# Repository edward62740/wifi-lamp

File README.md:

# WMNS Lamp

This is an mood lamp that takes ambient light readings from a database and adjusts its brightness and state accordingly. Extention of [WMNS](https://github.com/edward62740/Wireless-Mesh-Network-System).

## Description
Self-explanatory project which feeds off existing real-time data to decide it's brightness level.
Hardware based off ESP8266 with USB bridge and orange LED with driver. Enclosure printed (SLA) from black and clear resin.

</br>
Code should be modified based off desired operation. In this case, the lamp is set to activate at between 2 and 30 lux, which translates to dawn and dusk.

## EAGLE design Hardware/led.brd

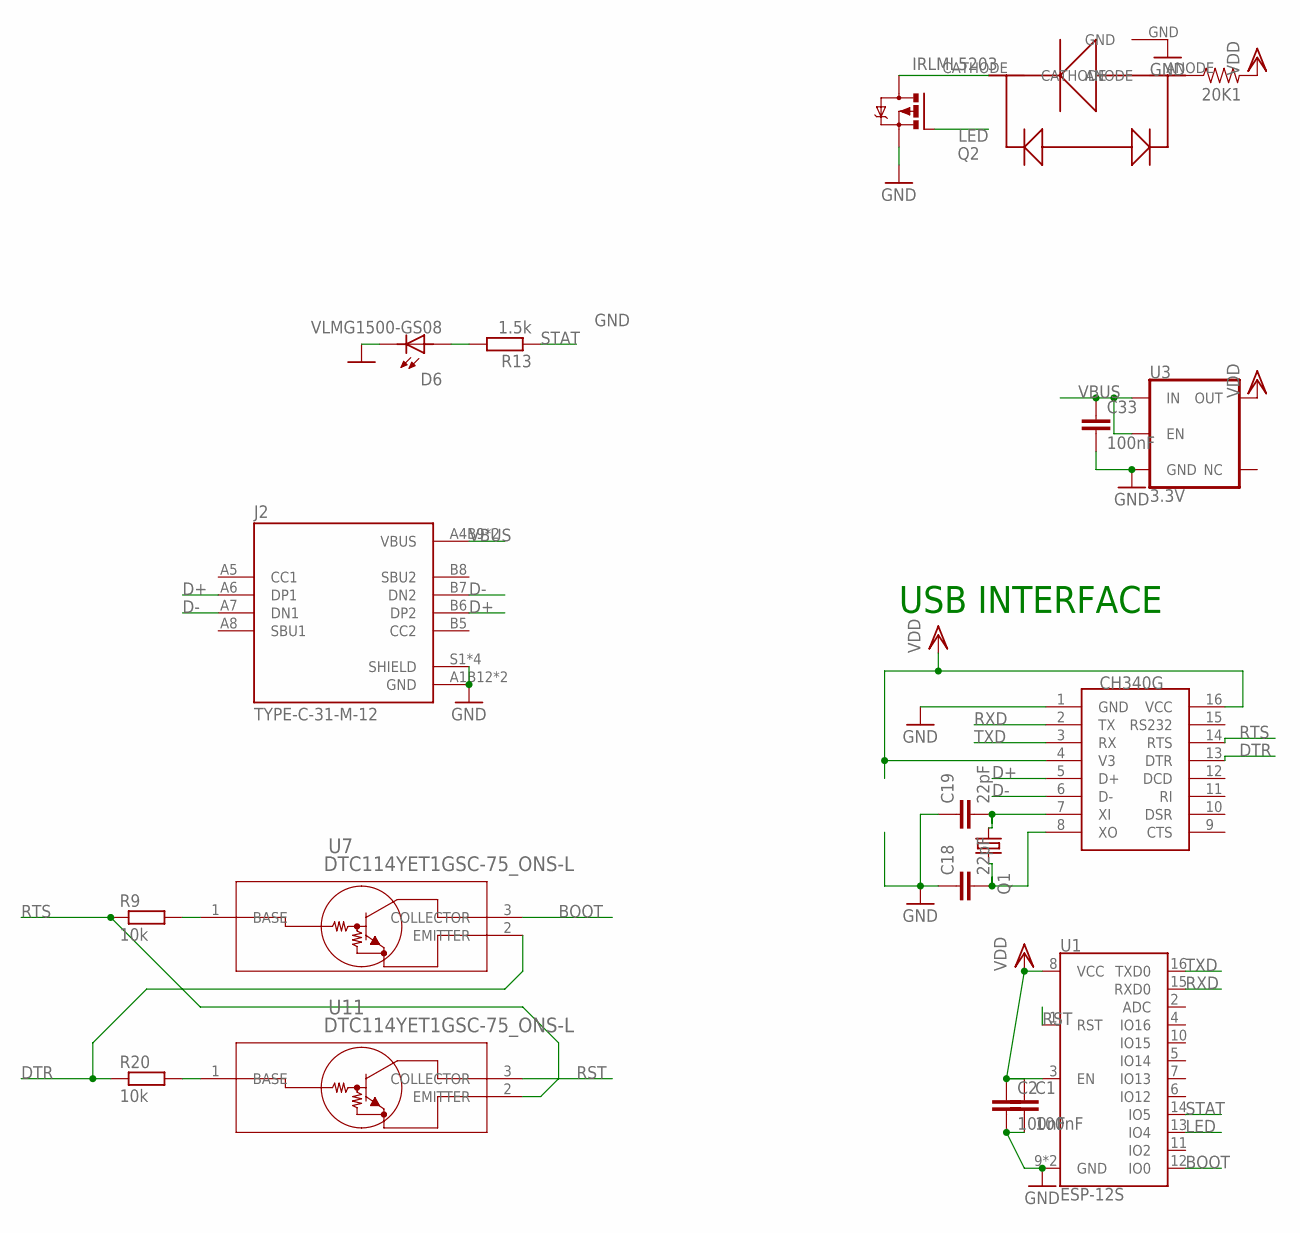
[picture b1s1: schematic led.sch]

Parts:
20K1: 0.05; 1210
C1, C2, C33: 100nF; C0402
C18, C19: 22pF; C0402
D6: VLMG1500-GS08; LEDC1005X35N
J2: TYPE-C-31-M-12; HRO_TYPE-C-31-M-12
Q1: KX-7; 3.2X2.5_KX-7
Q2: IRLML5203; MICRO3
R9, R20: 10k; R0402
R13: 1.5k; R0402
U1: ESP-12S
U3: 3.3V; SOT23-5
U5: H; SOIC16
U7, U11: DTC114YET1GSC-75_ONS-L; SC-75_ONS-L
U$1: ELSW(1W)

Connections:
BOOT: U1.12 (IO0), U7.3 (COLLECTOR)
D+: J2.A6 (DP1), J2.B6 (DP2), U5.5 (D+)
D-: J2.A7 (DN1), J2.B7 (DN2), U5.6 (D-)
DTR: R20.1, U5.13 (DTR), U7.2 (EMITTER)
GND: C1.2, C2.2, C18.1, C19.1, C33.2, D6.2, J2.A1B12 (GND), J2.B1A12 (GND), J2.S1 (SHIELD), J2.S2 (SHIELD), J2.S3 (SHIELD), J2.S4 (SHIELD), Q2.2 (S), U1.9 (GND), U1.P$1 (GND), U3.2 (GND), U5.1 (GND), U$1.GND
LED: Q2.1 (G), U1.13 (IO4)
unnamed: 20K1.1, U$1.ANODE
unnamed: Q2.3 (D), U$1.CATHODE
unnamed: C18.2, Q1.3 (2), U5.8 (XO)
unnamed: C19.2, Q1.1, U5.7 (XI)
unnamed: D6.1, R13.2
unnamed: R20.2, U11.1 (BASE)
unnamed: R9.2, U7.1 (BASE)
RST: U1.1 (RST), U11.3 (COLLECTOR)
RTS: R9.1, U5.14 (RTS), U11.2 (EMITTER)
RXD: U1.15 (RXD0), U5.2 (TX)
STAT: R13.1, U1.14 (IO5)
TXD: U1.16 (TXD0), U5.3 (RX)
VBUS: C33.1, J2.A4B9 (VBUS), J2.B4A9 (VBUS), U3.1 (IN), U3.3 (EN)
VDD: 20K1.2, C1.1, C2.1, U1.3 (EN), U1.8 (VCC), U3.5 (OUT), U5.4 (V3), U5.16 (VCC)

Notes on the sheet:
USB INTERFACE

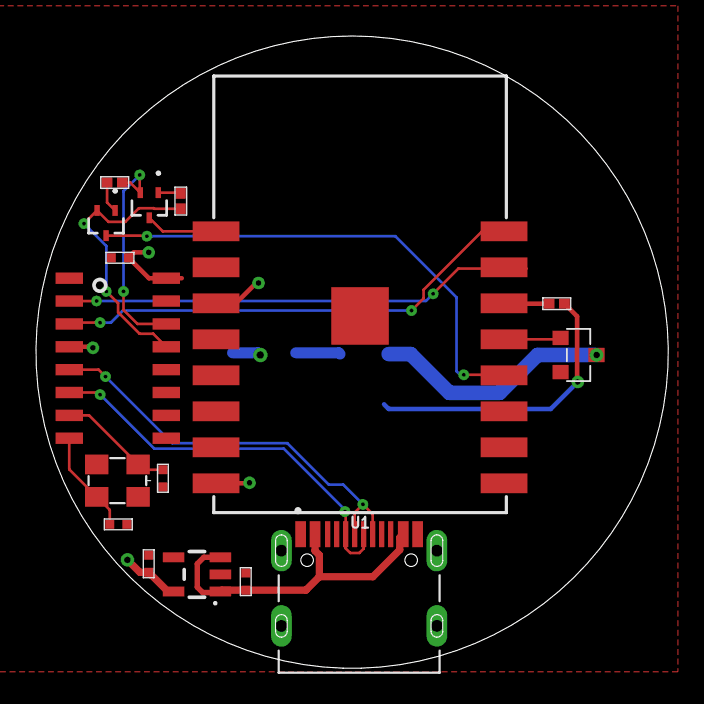
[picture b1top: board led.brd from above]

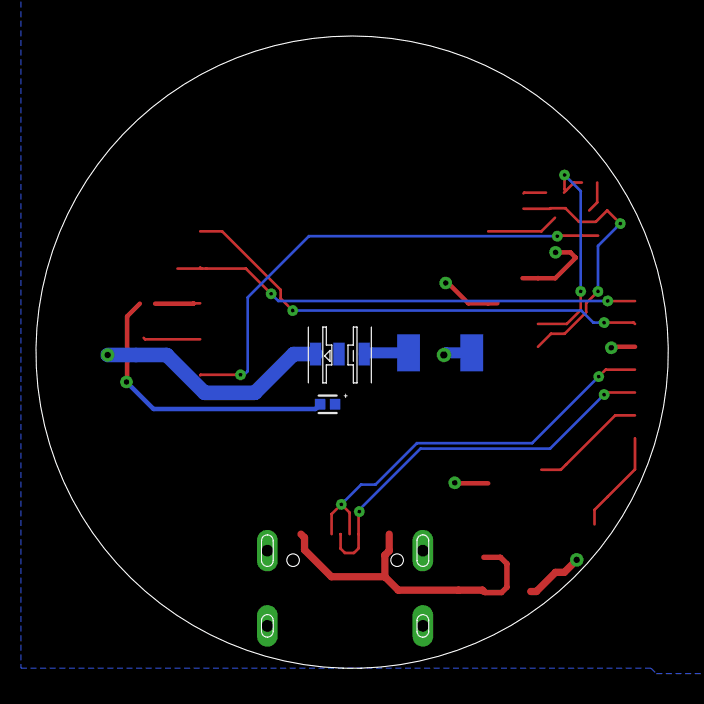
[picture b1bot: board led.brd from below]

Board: 4 copper layers, 35.1 x 35.1 mm, 19 parts (3 on the bottom side), 20 nets.

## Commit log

2022-02-12 First update
2022-02-24 Update caa 240222

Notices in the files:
parts and their libraries:
SparkFun-Resistors: Licensing: Creative Commons ShareAlike 4.0 International - https://creativecommons.org/licenses/by-sa/4.0
crystal-geyer_V1_0: Copyright: Geyer-Electronic
COPYRIGHT: Copyright (C) 2018 Accelerated Designs. All rights reserved
